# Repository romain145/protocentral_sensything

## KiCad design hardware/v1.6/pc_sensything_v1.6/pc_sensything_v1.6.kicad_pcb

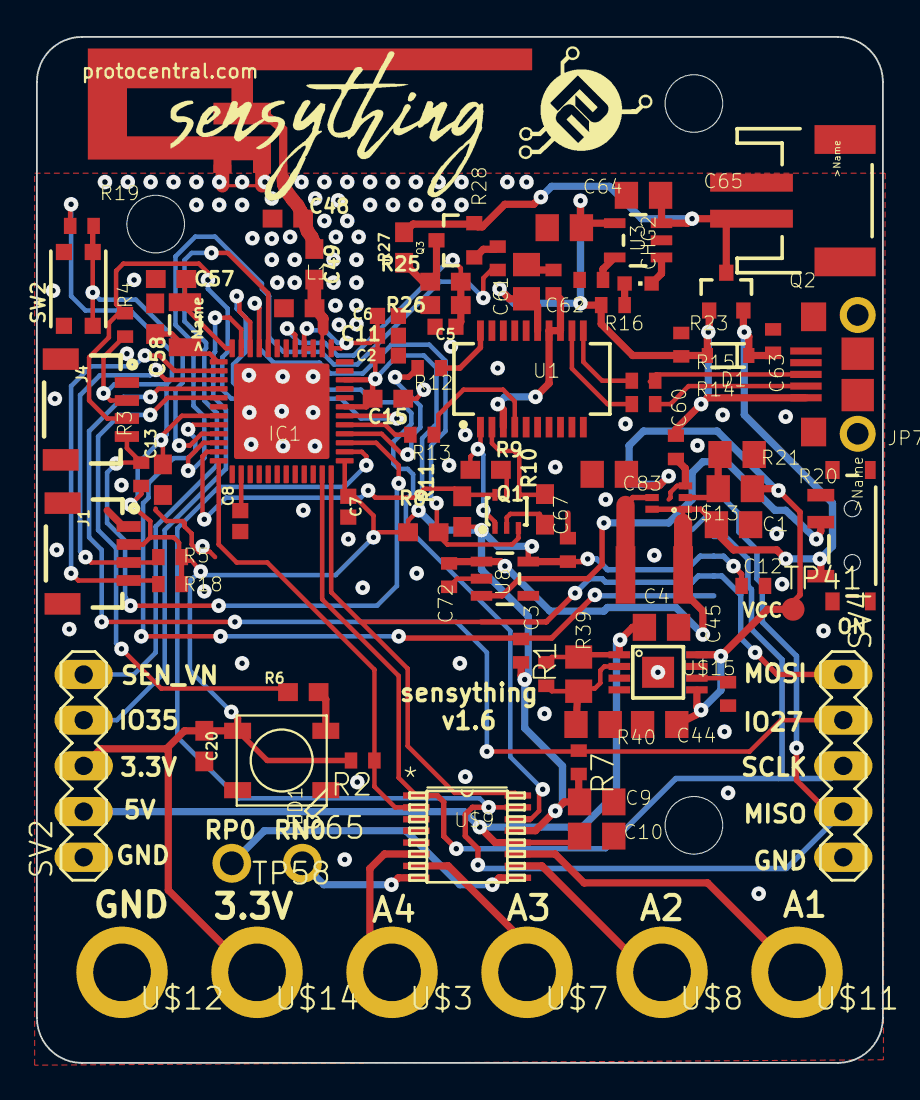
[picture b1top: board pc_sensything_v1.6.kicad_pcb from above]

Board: 2 copper layers, 47.0 x 57.0 mm, 102 parts (0 on the bottom side), 61 nets.

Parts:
@HOLE0, @HOLE1, @HOLE2: (no value)
C1, C64, C65, C83: 4.7u; C0805
C2, C5, C6, C7, C8, C11: 0.1uF; 0402
C3, C45: 10n; C0402
C4, C44: 10u; C0805
C9, C10: 100nF; C0805
C12: 100nF; C0402
C13, C15: 10uF; 0603
C20: 0.1uF; 0603
C48: 2.4pF; 0603
C49: 5.6pF; 0603
C57, C58: 15pF; 0603
C60, C62: 0.1uF; C0402
C61: 10uF; C0805
C63: 1.0uF; C0402
C67: 2.2uF; C0402
C72: 1u; C0402
CHG2: RED; CHIPLED_0603
D1: BAT20J; SOD-323
E1: ANTENNA; TRACE_ANTENNA_2.4GHZ_25.7MM_TUNED
IC1: ESP32-PICO-D4; QFN48
J1: Qwiic1; 1X04_1MM_RA
J4: Qwiic2; 1X04_1MM_RA
JP6: S2B-PH-SM4-TB(LF) (SN); JST-2-SMD
JP7: MICRO-B
L1: 2.7nH; 0603
LED1: WS2812B5050; WS2812B
LOGO2: OSHW_LOGO_FILLX0200-NT; OSHW_FILLX200_NOTEXT
Q1: MBT3904DW1T1; SC70-6
Q2, Q3: 2.5A/30V; SOT23-3
R1, R2, R3, R4, R5, R7, R18, R19, R23: 10K; R0402
R6, R8, R9, R10, R11, R25, R26: 10k; 0603
R12, R13: 1K; R0402
R14, R15: 27; R0402
R16: 330R; R0402
R17: 1k; R0402
R20: 60K; R0805
R21: 10K; R0805
R27: DNP; 0603
R28: DNP; R0402
R39: 162k; R0805
R40: 51.1k; R0805
S2: PCM12SMTR; SWITCH-SPST-SMD-A
SV2, SV4: MA05-1
SW2: KMR2; BTN_KMR2_4.6X2.8
TP41: TPSQB1,27; B1,27
TP58, TP65: PTR1PAD1-13; P1-13
U1: FTS31XS-U; SSOP20_L
U3: MCP73831; SOT23-5
U8: AP2112K-3.3V; SOT23-5
U$1: LQH3NPN1R0NJ0; LQH3NP
U$2: SENSYTHING
U$3, U$7, U$8, U$11, U$12, U$14: SENSYTHING_CON
U$4: SENSYTHING_SMALL
U$5, U$19: PROTY-LOGO; LOGO-PROTY
U$9: ADS1220; TSSOP-16
U$13: TPS61220; SC-70-6
U$15: TPS7A4901; S-PDSO-G08
U$20: SD_CARD_ADAPTER; SD-105162
U$26: PROTY_LOGO_WITH_TEXT; PROTY_WITH_TEXT@1
Y1: 32.768kHz; CRYSTAL-SMD-3.2X1.5MM

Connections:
3.3V: C2.1, C6.1, C7.1, C9.1, C11.1, C12.1, C13.1, C15.1, C20.1, C67.1, IC1.1, IC1.3, IC1.4, IC1.19, IC1.37, IC1.43, IC1.46, J1.2, J4.2, LED1.1-VDD, R1.2, R2.2, R3.2, R4.2, R5.2, R7.2, R8.2, R11.2, R18.2, R19.2, SV2.3, U8.5, U$9.13, U$14.TP, U$20.4
+5V: C3.1, C4.1, C10.1, R39.2, SV2.2, U$9.12, U$15.1
/pc_sensything_v1.6_1/0: IC1.23, Q1.6, R11.1
/pc_sensything_v1.6_1/3.3V_F: C62.1, U1.3, U1.13, U1.14
/pc_sensything_v1.6_1/32K_XN: C58.2, IC1.13, Y1.P$2
/pc_sensything_v1.6_1/32K_XP: C57.2, IC1.12, Y1.P$1
/pc_sensything_v1.6_1/AIN0: U$9.11, U$11.TP
/pc_sensything_v1.6_1/AIN1: U$8.TP, U$9.10
/pc_sensything_v1.6_1/AIN2: U$7.TP, U$9.7
/pc_sensything_v1.6_1/AIN3: U$3.TP, U$9.6
/pc_sensything_v1.6_1/BAT_MON: C5.1, IC1.5, R25.1, R26.2
/pc_sensything_v1.6_1/BUTTON: IC1.21, R19.1, SW2.B, SW2.B'
/pc_sensything_v1.6_1/CHIP_PU: IC1.9, Q1.3, R8.1
/pc_sensything_v1.6_1/CS2: IC1.20, R1.1, U$20.2
/pc_sensything_v1.6_1/CS3: IC1.16, R7.1, SV4.2
/pc_sensything_v1.6_1/D+: JP7.3, R15.1
/pc_sensything_v1.6_1/D-: JP7.2, R14.1
/pc_sensything_v1.6_1/DTR: Q1.1, R9.1, U1.1
/pc_sensything_v1.6_1/MISO: IC1.38, SV4.4, U$9.15, U$20.7
/pc_sensything_v1.6_1/MON_EN: Q3.1, R28.1
/pc_sensything_v1.6_1/MOSI: IC1.36, SV4.1, U$9.16, U$20.3
/pc_sensything_v1.6_1/REFN0: TP65.TP, U$9.8
/pc_sensything_v1.6_1/REFP0: TP58.TP, U$9.9
/pc_sensything_v1.6_1/RTS: Q1.4, R10.1, U1.2
/pc_sensything_v1.6_1/RXD: R13.2, U1.4
/pc_sensything_v1.6_1/SCL: IC1.39, J4.4, R3.1
/pc_sensything_v1.6_1/SCL1: IC1.14, J1.4, R18.1
/pc_sensything_v1.6_1/SCLK: IC1.35, SV4.3, U$9.1, U$20.5
/pc_sensything_v1.6_1/SDA: IC1.42, J4.3, R4.1
/pc_sensything_v1.6_1/SDA1: IC1.15, J1.3, R5.1
/pc_sensything_v1.6_1/TXD: R12.2, U1.20
/pc_sensything_v1.6_1/U0RXD: IC1.40, R12.1
/pc_sensything_v1.6_1/U0TXD: IC1.41, R13.1
/pc_sensything_v1.6_1/WS2812: IC1.17, R6.2
/pc_sensything_v1.6_1/~CS1: IC1.24, R2.1, U$9.2
/pc_sensything_v1.6_1/~DRDY: IC1.10, U$9.14
/pc_sensything_v1.6_2/EN: S2.2, U8.3
GND: C1.2, C2.2, C4.2, C5.2, C6.2, C7.2, C8.2, C9.2, C10.2, C11.2, C12.2, C13.2, C15.2, C20.2, C44.2, C45.2, C48.2, C57.1, C58.1, C60.2, C61.2, C62.2, C63.2, C64.2, C65.2, C67.2, C72.1, C83.2, E1.GND, E1.GND2, IC1.EXP, J1.1, J4.1, JP6.1, JP7.5, JP7.P$5, JP7.P$6, L1.2, LED1.3-GND, R17.1, R21.2, R23.1, R26.1, R40.1, S2.1, SV2.1, SV4.5, SW2.A, U1.6, U1.16, U3.2, U8.2, U$9.3, U$9.4, U$9.5, U$12.TP, U$13.3, U$15.4, U$15.TH, U$20.6, U$20.10, U$20.11, U$20.12, U$20.13
unnamed: C3.2, R39.1, R40.2, U$15.2
unnamed: C8.1, IC1.26
unnamed: C45.1, U$15.6
unnamed: C48.1, C49.2, E1.ANT
unnamed: C49.1, IC1.2, L1.1
unnamed: CHG2.A, R16.2
unnamed: CHG2.C, U3.1
unnamed: IC1.8, SV2.5
unnamed: IC1.11, SV2.4
unnamed: IC1.22, R28.2
unnamed: LED1.4-DIN, R6.1
unnamed: Q1.2, R10.2
unnamed: Q1.5, R9.2
unnamed: Q3.3, R25.2, R27.1
unnamed: R14.2, U1.12
unnamed: R15.2, U1.11
unnamed: R17.2, U3.5
unnamed: R20.2, R21.1, U$13.2
unnamed: U$1.P$2, U$13.5
VBAT: C65.1, JP6.2, Q2.3, Q3.2, R27.2, U3.3
VCC: C44.1, C83.1, R20.1, TP41.TP, U$13.4, U$15.5, U$15.8
VIN: C1.1, C63.1, C72.2, D1.C, Q2.2, S2.3, U8.1, U$1.P$1, U$13.1, U$13.6
VUSB: C60.1, C61.1, C64.1, D1.A, JP7.1, Q2.1, R16.1, R23.2, U1.15, U3.4

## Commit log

2020-09-16 KiCAD Export Changed R17 to reduce LiPo charge current for 410mAh battery
2020-09-16 Example running on Sensything. WS2812 LED green super dim.
2020-09-25 Sketches running on Sensything.
